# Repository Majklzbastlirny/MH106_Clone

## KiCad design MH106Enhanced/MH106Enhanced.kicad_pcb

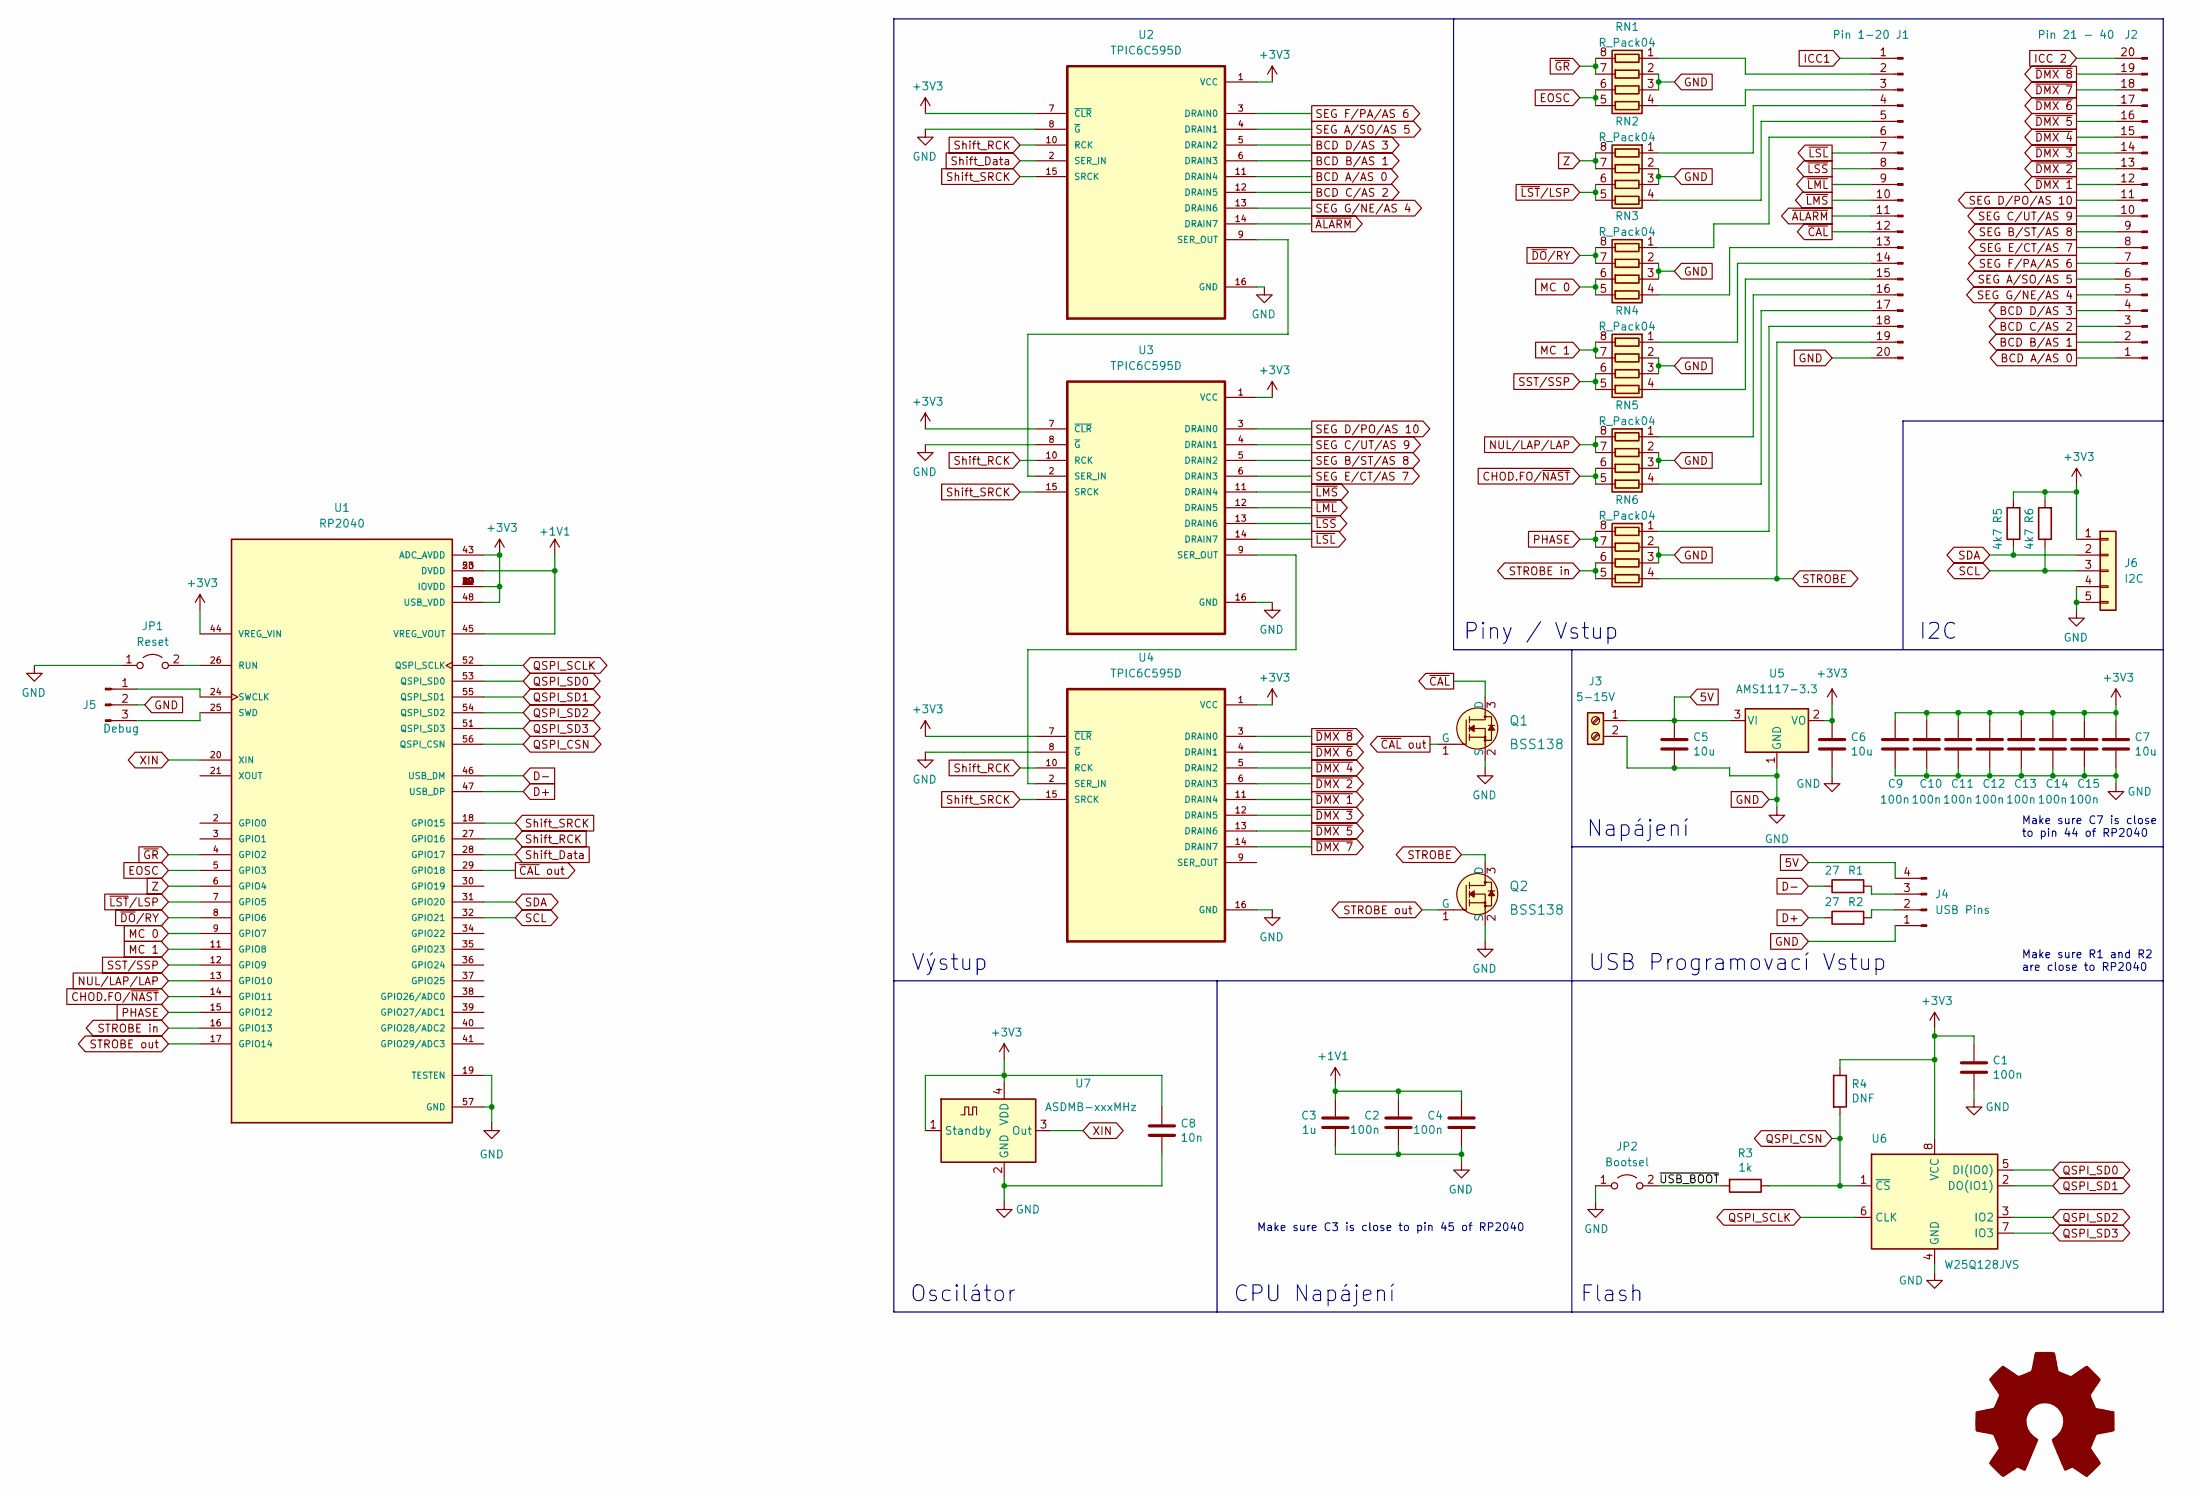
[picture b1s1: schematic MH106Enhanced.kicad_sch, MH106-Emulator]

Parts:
C1, C2, C4, C9, C10, C11, C12, C13, C14, C15: 100n; C_0603_1608Metric_Pad1.08x0.95mm_HandSolder
C3: 1u; C_0603_1608Metric_Pad1.08x0.95mm_HandSolder
C5, C6, C7: 10u; C_0603_1608Metric_Pad1.08x0.95mm_HandSolder
C8: 10n; C_0603_1608Metric_Pad1.08x0.95mm_HandSolder
J1: Pin 1-20; PinHeader_1x20_P2.54mm_Vertical
J2: Pin 21 - 40; PinHeader_1x20_P2.54mm_Vertical
J3: 5-15V; TerminalBlock_Phoenix_MPT-0,5-2-2.54_1x02_P2.54mm_Horizontal
J4: USB Pins; PinHeader_1x04_P1.27mm_Vertical
J5: Debug; PinHeader_1x03_P1.27mm_Vertical
J6: I2C; PinHeader_1x05_P2.54mm_Vertical
JP1: Reset; SolderJumper-2_P1.3mm_Open_RoundedPad1.0x1.5mm
JP2: Bootsel; SolderJumper-2_P1.3mm_Open_RoundedPad1.0x1.5mm
Q1, Q2: BSS138; TSOT-23_HandSoldering; MPN BSS138; Digi-Key_PN BSS138CT-ND
R1, R2: 27; R_0603_1608Metric_Pad0.98x0.95mm_HandSolder
R3: 1k; R_0603_1608Metric_Pad0.98x0.95mm_HandSolder
R4: DNF; R_0603_1608Metric_Pad0.98x0.95mm_HandSolder
R5, R6: 4k7; R_0603_1608Metric_Pad0.98x0.95mm_HandSolder
RN1, RN2, RN3, RN4, RN5, RN6: R_Pack04; R_Array_Convex_4x0603
U1: RP2040; QFN40P700X700X90-57N; PARTREV 1.6.1
U2, U3, U4: TPIC6C595D; SOIC127P600X175-16N
U5: AMS1117-3.3; SOT-223-3_TabPin2
U6: W25Q128JVS; SOIC-8W_5.3x5.3mm_P1.27mm
U7: ASDMB-xxxMHz; Oscillator_SMD_Abracon_ASDMB-4Pin_2.5x2.0mm

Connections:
5V: C5.1, J3.1, J4.4, U5.3 (VI)
+1V1: C2.1, C3.1, C4.1, U1.23 (DVDD), U1.45 (VREG_VOUT), U1.50 (DVDD)
+3V3: C1.1, C6.1, C7.1, C8.1, C9.1, C10.1, C11.1, C12.1, C13.1, C14.1, C15.1, J6.1, R4.1, R5.2, R6.2, U1.1 (IOVDD), U1.10 (IOVDD), U1.22 (IOVDD), U1.33 (IOVDD), U1.42 (IOVDD), U1.43 (ADC_AVDD), U1.44 (VREG_VIN), U1.48 (USB_VDD), U1.49 (IOVDD), U2.1 (VCC), U2.7 (~CLR), U3.1 (VCC), U3.7 (~CLR), U4.1 (VCC), U4.7 (~CLR), U5.2 (VO), U6.8 (VCC), U7.1 (Standby), U7.4 (VDD)
/~USB_BOOT: JP2.2 (B), R3.2
BCD A/AS 0: J2.1, U2.11 (DRAIN4)
BCD B/AS 1: J2.2, U2.6 (DRAIN3)
BCD C/AS 2: J2.3, U2.12 (DRAIN5)
BCD D/AS 3: J2.4, U2.5 (DRAIN2)
CHOD.FO/~NAST: RN5.5 (R4.2), RN5.6 (R3.2), U1.14 (GPIO11)
D+: R2.1, U1.47 (USB_DP)
D-: R1.1, U1.46 (USB_DM)
EOSC: RN1.5 (R4.2), RN1.6 (R3.2), U1.5 (GPIO3)
GND: C1.2, C2.2, C3.2, C4.2, C5.2, C6.2, C7.2, C8.2, C9.2, C10.2, C11.2, C12.2, C13.2, C14.2, C15.2, J1.20, J3.2, J4.1, J5.2, J6.4, J6.5, JP1.1 (A), JP2.1 (A), Q1.2 (S), Q2.2 (S), RN1.2 (R2.1), RN1.3 (R3.1), RN2.2 (R2.1), RN2.3 (R3.1), RN3.2 (R2.1), RN3.3 (R3.1), RN4.2 (R2.1), RN4.3 (R3.1), RN5.2 (R2.1), RN5.3 (R3.1), RN6.2 (R2.1), RN6.3 (R3.1), U1.19 (TESTEN), U1.57 (GND), U2.8 (~G), U2.16 (GND), U3.8 (~G), U3.16 (GND), U4.8 (~G), U4.16 (GND), U5.1 (GND), U6.4 (GND), U7.2 (GND)
ICC1: J1.1
ICC 2: J2.20
MC 0: RN3.5 (R4.2), RN3.6 (R3.2), U1.9 (GPIO7)
MC 1: RN4.7 (R2.2), RN4.8 (R1.2), U1.11 (GPIO8)
NUL/LAP/LAP: RN5.7 (R2.2), RN5.8 (R1.2), U1.13 (GPIO10)
unnamed: J1.2, RN1.1 (R1.1)
unnamed: J1.3, RN1.4 (R4.1)
unnamed: J1.4, RN2.1 (R1.1)
unnamed: J1.5, RN2.4 (R4.1)
unnamed: J1.6, RN3.1 (R1.1)
unnamed: J1.13, RN3.4 (R4.1)
unnamed: J1.14, RN4.1 (R1.1)
unnamed: J1.15, RN4.4 (R4.1)
unnamed: J1.16, RN5.1 (R1.1)
unnamed: J1.17, RN5.4 (R4.1)
unnamed: J1.18, RN6.1 (R1.1)
unnamed: J4.2, R2.2
unnamed: J4.3, R1.2
unnamed: J5.1, U1.24 (SWCLK)
unnamed: J5.3, U1.25 (SWD)
unnamed: JP1.2 (B), U1.26 (RUN)
unnamed: U2.9 (SER_OUT), U3.2 (SER_IN)
unnamed: U3.9 (SER_OUT), U4.2 (SER_IN)
PHASE: RN6.7 (R2.2), RN6.8 (R1.2), U1.15 (GPIO12)
QSPI_CSN: R3.1, R4.2, U1.56 (QSPI_CSN), U6.1 (~CS)
QSPI_SCLK: U1.52 (QSPI_SCLK), U6.6 (CLK)
QSPI_SD0: U1.53 (QSPI_SD0), U6.5 (DI(IO0))
QSPI_SD1: U1.55 (QSPI_SD1), U6.2 (DO(IO1))
QSPI_SD2: U1.54 (QSPI_SD2), U6.3 (IO2)
QSPI_SD3: U1.51 (QSPI_SD3), U6.7 (IO3)
SCL: J6.3, R6.1, U1.32 (GPIO21)
SDA: J6.2, R5.1, U1.31 (GPIO20)
SEG A/SO/AS 5: J2.6, U2.4 (DRAIN1)
SEG B/ST/AS 8: J2.9, U3.5 (DRAIN2)
SEG C/UT/AS 9: J2.10, U3.4 (DRAIN1)
SEG D/PO/AS 10: J2.11, U3.3 (DRAIN0)
SEG E/CT/AS 7: J2.8, U3.6 (DRAIN3)
SEG F/PA/AS 6: J2.7, U2.3 (DRAIN0)
SEG G/NE/AS 4: J2.5, U2.13 (DRAIN6)
SST/SSP: RN4.5 (R4.2), RN4.6 (R3.2), U1.12 (GPIO9)
STROBE: J1.19, Q2.3 (D), RN6.4 (R4.1)
STROBE in: RN6.5 (R4.2), RN6.6 (R3.2), U1.16 (GPIO13)
STROBE out: Q2.1 (G), U1.17 (GPIO14)
Shift_Data: U1.28 (GPIO17), U2.2 (SER_IN)
Shift_RCK: U1.27 (GPIO16), U2.10 (RCK), U3.10 (RCK), U4.10 (RCK)
Shift_SRCK: U1.18 (GPIO15), U2.15 (SRCK), U3.15 (SRCK), U4.15 (SRCK)
XIN: U1.20 (XIN), U7.3 (Out)
Z: RN2.7 (R2.2), RN2.8 (R1.2), U1.6 (GPIO4)
~ALARM: J1.11, U2.14 (DRAIN7)
~CAL: J1.12, Q1.3 (D)
~CAL out: Q1.1 (G), U1.29 (GPIO18)
~DMX 1: J2.12, U4.11 (DRAIN4)
~DMX 2: J2.13, U4.6 (DRAIN3)
~DMX 3: J2.14, U4.12 (DRAIN5)
~DMX 4: J2.15, U4.5 (DRAIN2)
~DMX 5: J2.16, U4.13 (DRAIN6)
~DMX 6: J2.17, U4.4 (DRAIN1)
~DMX 7: J2.18, U4.14 (DRAIN7)
~DMX 8: J2.19, U4.3 (DRAIN0)
~DO/RY: RN3.7 (R2.2), RN3.8 (R1.2), U1.8 (GPIO6)
~GR: RN1.7 (R2.2), RN1.8 (R1.2), U1.4 (GPIO2)
~LML: J1.9, U3.12 (DRAIN5)
~LMS: J1.10, U3.11 (DRAIN4)
~LSL: J1.7, U3.14 (DRAIN7)
~LSS: J1.8, U3.13 (DRAIN6)
~LST/LSP: RN2.5 (R4.2), RN2.6 (R3.2), U1.7 (GPIO5)

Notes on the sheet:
Make sure C3 is close to pin 45 of RP2040
USB Programovací Vstup
Make sure R1 and R2 are close to RP2040
I2C
Oscilátor
CPU Napájení
Make sure C7 is close to pin 44 of RP2040
Napájení
Výstup
Flash
Piny / Vstup

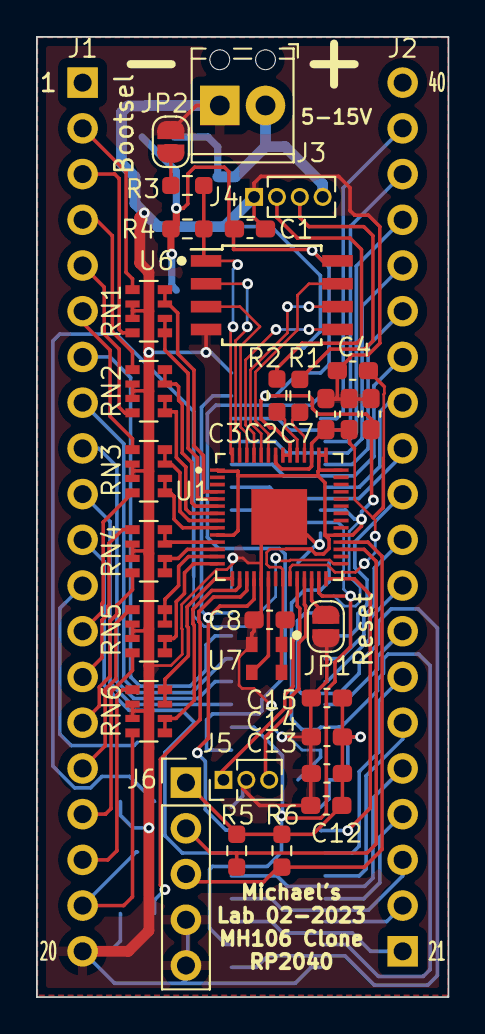
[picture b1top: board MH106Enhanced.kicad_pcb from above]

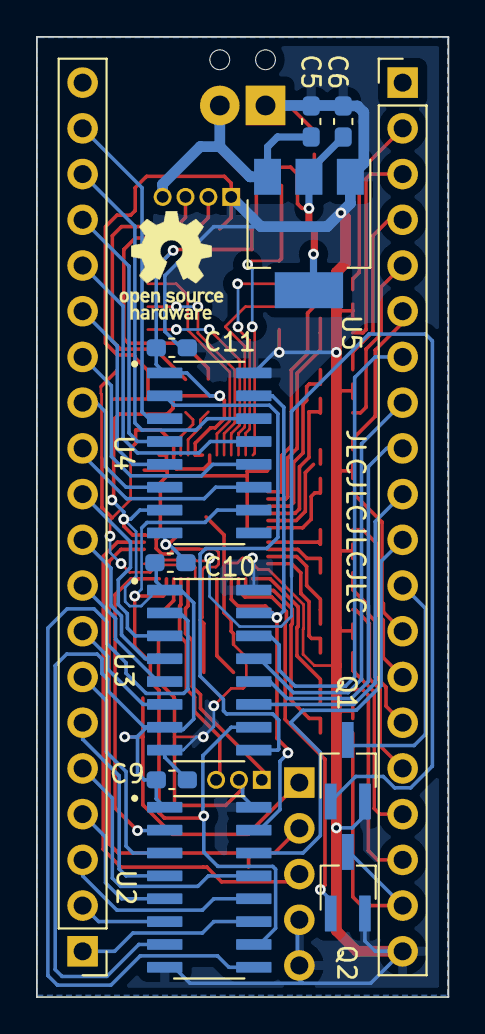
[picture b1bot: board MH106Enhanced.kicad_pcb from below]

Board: 2 copper layers, 22.9 x 53.3 mm, 44 parts (13 on the bottom side), 77 nets.

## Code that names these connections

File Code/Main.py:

#Code for emulating MH106 clock IC with micropython and RP2040
#Author: Michal Basler
#Date: 2023-01-28
#Version: 0.1
#License: GPL v3.0

#Description:
#This code is intended to emulate MH106 clock IC with micropython and RP2040. It can display time (HH:MM:SS), Date/Calendar (DD.MM.YYY), Stopwatch (MM:SS:MS / HH:MM:SS after minute overflow) and Alarm
#It has 12 input pins and 26 output pins, 24 driven by three TPIC6C595 shift registers in series and 2 driven by 2 N channel mosfets.
#Using both cores. Core 0 is used for reading inputs and writing outputs, core 1 is used handling time and other tasks.

#Pin assignments:
#OUTPUTS:
#SHIFT_RCK = GPIO(16) register clock
#SHIFT_SRCK = GPIO(15) shift register clock
#SHIFT_DATA = GPIO(17) serial data

#Pins 0-7: TPIC6C595 1 (SEG F/PA/AS 6, SEG A/SO/AS 5, BCD D/AS 3, BCD B/AS 1, BCD A/AS 0, BCD C/AS 2, SEG G/NE/AS 4, !ALARM)
#Pins 0-7: TPIC6C595 2 (SEG D/PO/AS 10, SEG C/AS 9, SEG B/AS 8, SEG E/AS 7, !LMS, !LML, !LSS, !LSL)
#Pins 0-7: TPIC6C595 3 (!DMX 8, !DMX6, !DMX4, !DMX2, !DMX1, !DMX3, !DMX5, !DMX7)


#FET1: (!CAL out) = GPIO(18)
#FET2: (!strobe out) = GPIO(14)

#INPUTS:
#!GR = GPIO(2)
#EOSC = GPIO(3)
#Z = GPIO(4)
#!LST/LSP = GPIO(5)
#!DO/RY = GPIO(6)
#MC 0 = GPIO(7)
#MC 1 = GPIO(8)
#SST/SSP = GPIO(9)
#NUL/LAP/LAP = GPIO(10)
#CHOD.FO/!NAST = GPIO(11)
#PHASE = GPIO(12)
#STROBE in = GPIO(13)

#I2C: optional for future use (RTC DS3231)
#SDA = GPIO(20)
#SCL = GPIO(21)

#LIBRARIES:
import machine
import utime
import ustruct
import uasyncio
import ujson
import uos
import uerrno
import uio
import uarray

#CONSTANTS:
#Constants for shift register:
SHIFT_RCK = machine.Pin(16, machine.Pin.OUT) #register clock
SHIFT_SRCK = machine.Pin(15, machine.Pin.OUT) #shift register clock
SHIFT_DATA = machine.Pin(17, machine.Pin.OUT) #serial data

#I2C
i2c = machine.I2C(0, scl=machine.Pin(21), sda=machine.Pin(20), freq=400000)




#Routines and functions:
#Reading INPUTS:
def read_inputs(): #Each input is a variable, which is set to 1 if the input is high and 0 if the input is low
    global GR
    global EOSC
    global Z
    global LST_LSP
    global DO_RY
    global MC_0
    global MC_1
    global SST_SSP
    global NUL_LAP
    global CHOD_FO
    global PHASE
    global STROBE_IN
    GR = 1 if GPIO(2).value() else 0
    EOSC = 1 if GPIO(3).value() else 0
    Z = 1 if GPIO(4).value() else 0
    LST_LSP = 1 if GPIO(5).value() else 0
    DO_RY = 1 if GPIO(6).value() else 0
    MC_0 = 1 if GPIO(7).value() else 0
    MC_1 = 1 if GPIO(8).value() else 0
    SST_SSP = 1 if GPIO(9).value() else 0
    NUL_LAP = 1 if GPIO(10).value() else 0
    CHOD_FO = 1 if GPIO(11).value() else 0
    PHASE = 1 if GPIO(12).value() else 0
    STROBE_IN = 1 if GPIO(13).value() else 0

#Writing OUTPUTS:
def write_outputs(): #Each output is a variable, which is set to 1 if the output should be high and 0 if the output should be low
    global ALARM
    global BCD_A
    global BCD_B
    global BCD_C
    global BCD_D
    global SEG_A
    global SEG_B
    global SEG_C
    global SEG_D
    global SEG_E
    global SEG_F
    global SEG_G
    global CAL
    global LSS
    global LSL
    global LMS
    global LML
    global STROBE_OUT
    global DMX1
    global DMX2
    global DMX3
    global DMX4
    global DMX5
    global DMX6
    global DMX7
    global DMX8


    #Firstly clear all outputs:
    clear_outputs()

    #Then set the outputs:
    shift_data([DMX7,DMX5,DMX3,DMX1,DMX2,DMX4,DMX6,DMX8, LSL,LSS,LML,LMS,SEG_E,SEG_B,SEG_C,SEG_D, ALARM,SEG_G,SEG_C,SEG_A,SEG_B,SEG_D,SEG_A,SEG_F])
    GPIO(18).value(CAL) #setting FET1 (CAL)
    GPIO(14).value(STROBE_OUT) #setting FET2 (strobe out)

def shift_data(data):
    for bit in data:
        SHIFT_DATA.value(bit) #set the data bit
        SHIFT_RCK.on() #clock the data into the register
        SHIFT_RCK.off() 
    SHIFT_SRCK.on() #clock the register into the output
    SHIFT_SRCK.off() 

    
def clear_outputs(): #clears all outputs
    shift_data([0,0,0,0,0,0,0,0]*3) #clearing shift registers
    GPIO(18).off() #clearing FET1 (CAL)
    GPIO(14).off() #clearing FET2 (strobe out)



#MAIN CODE:
if __name__ == "__main__":
    #Bootup (run once):
    clear_outputs() #clear all outputs

    #Main loop:
    while True:
        read_inputs()
        write_outputs()
    

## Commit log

2023-01-26 Create PCB file
2023-01-26 placed first ic
2023-01-27 Schematic nearly done
2023-01-28 Nearly DONE
2023-01-28 PCB IS DONE
2023-01-28 First lines of code and minor PCB edit
2023-02-16 update
    Idunno what i've changed
